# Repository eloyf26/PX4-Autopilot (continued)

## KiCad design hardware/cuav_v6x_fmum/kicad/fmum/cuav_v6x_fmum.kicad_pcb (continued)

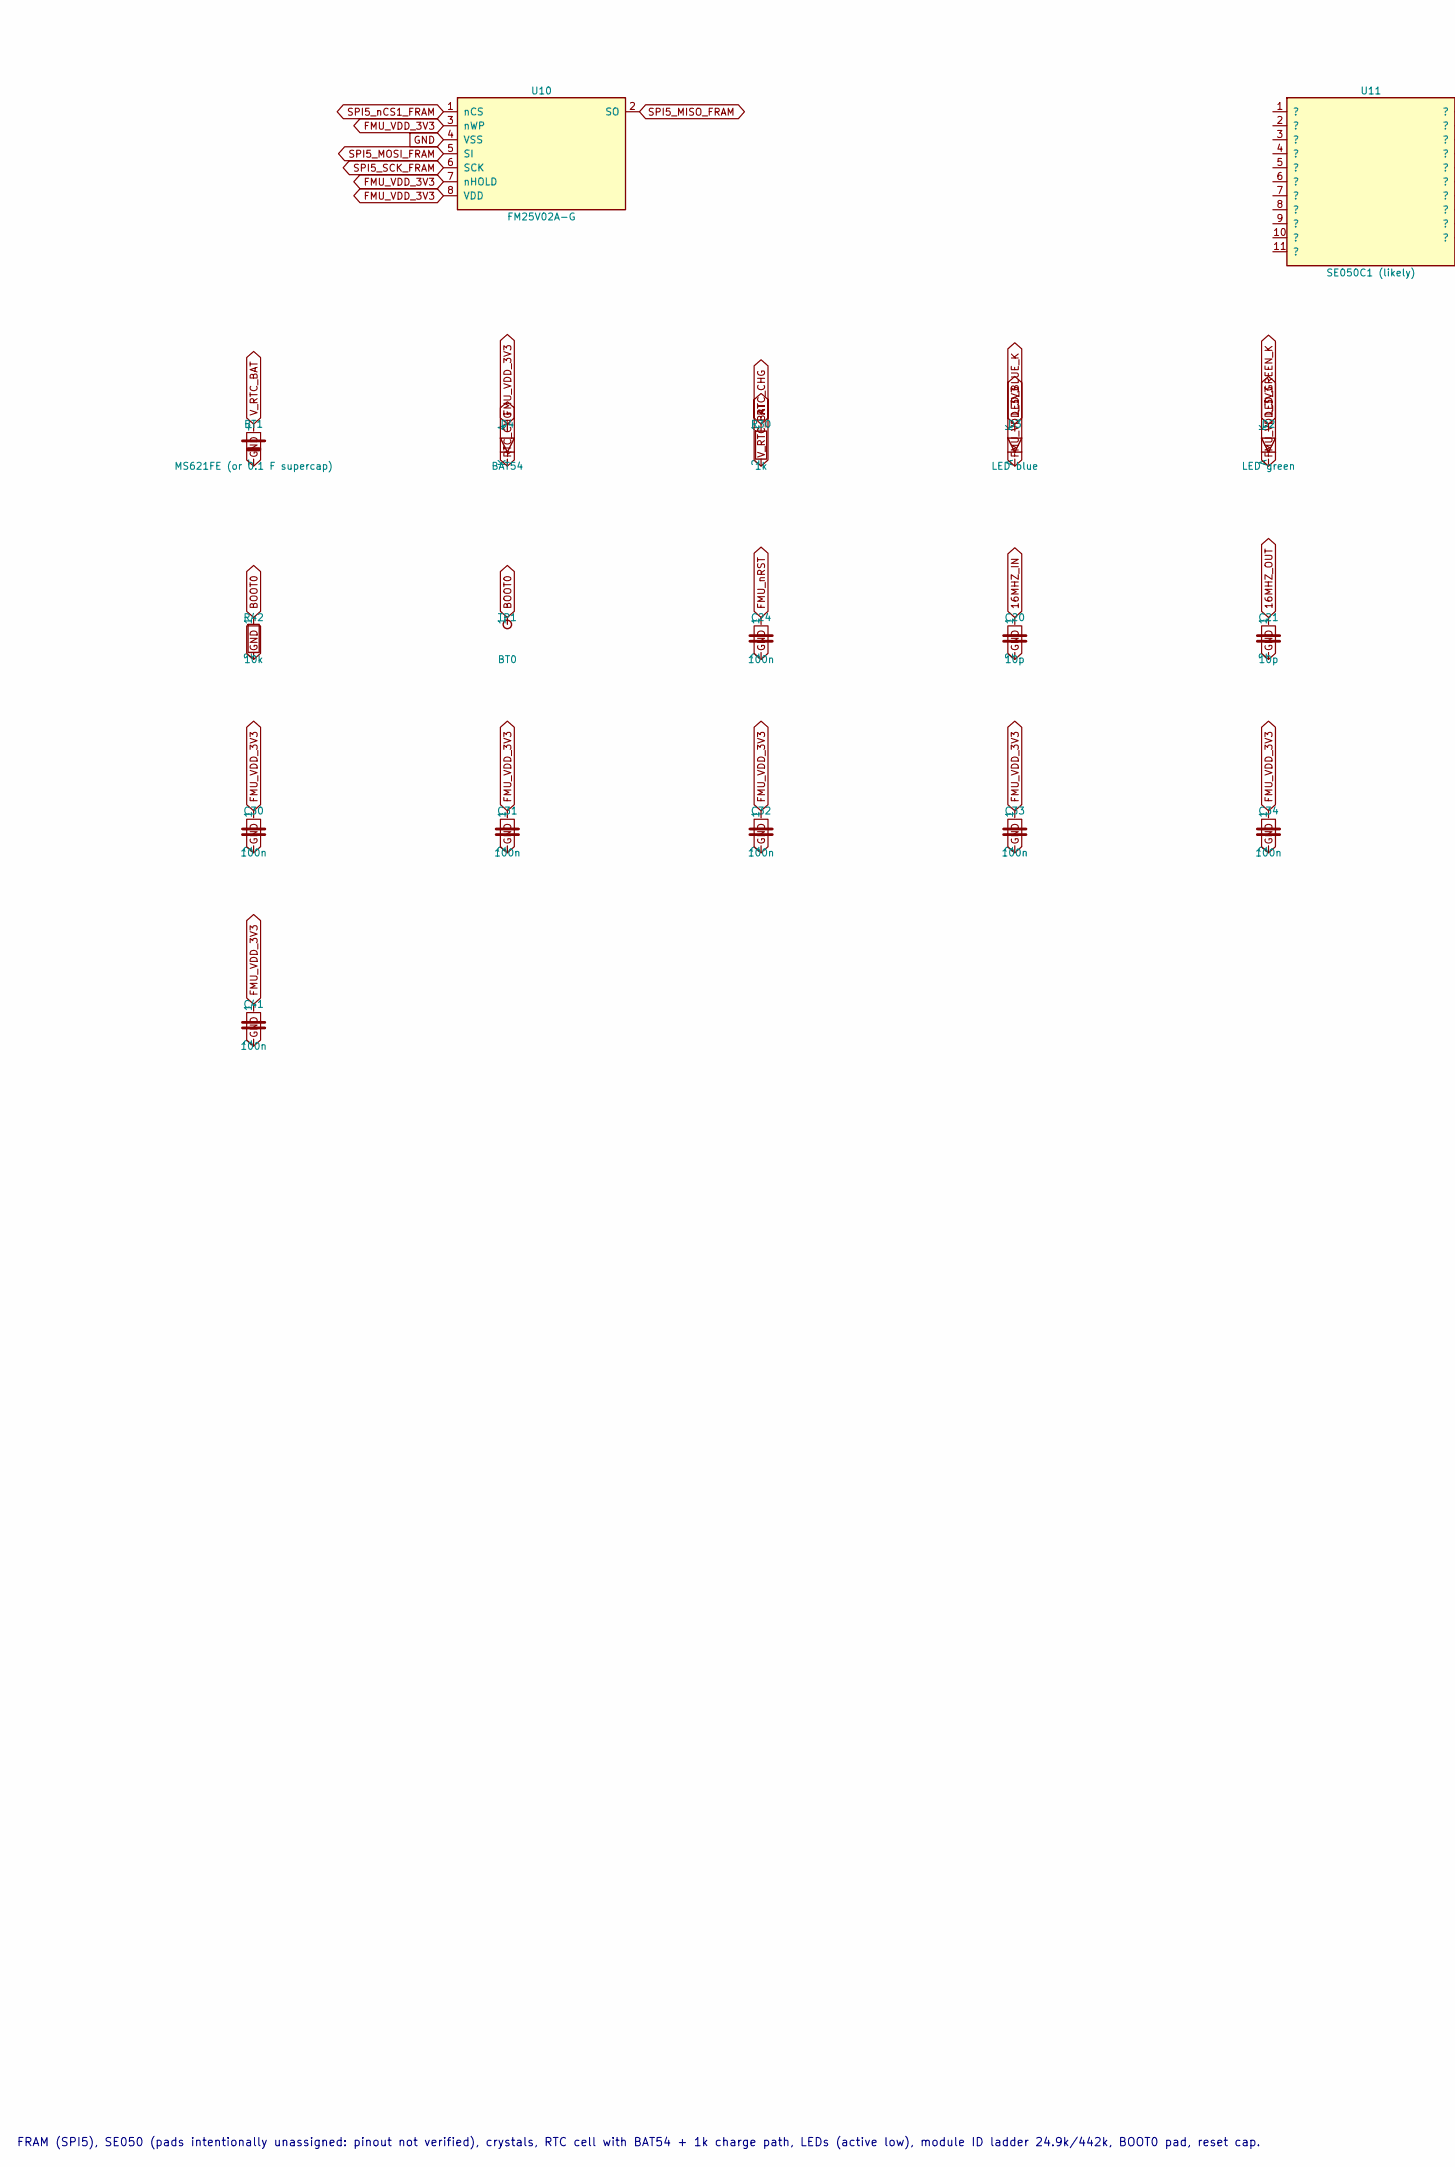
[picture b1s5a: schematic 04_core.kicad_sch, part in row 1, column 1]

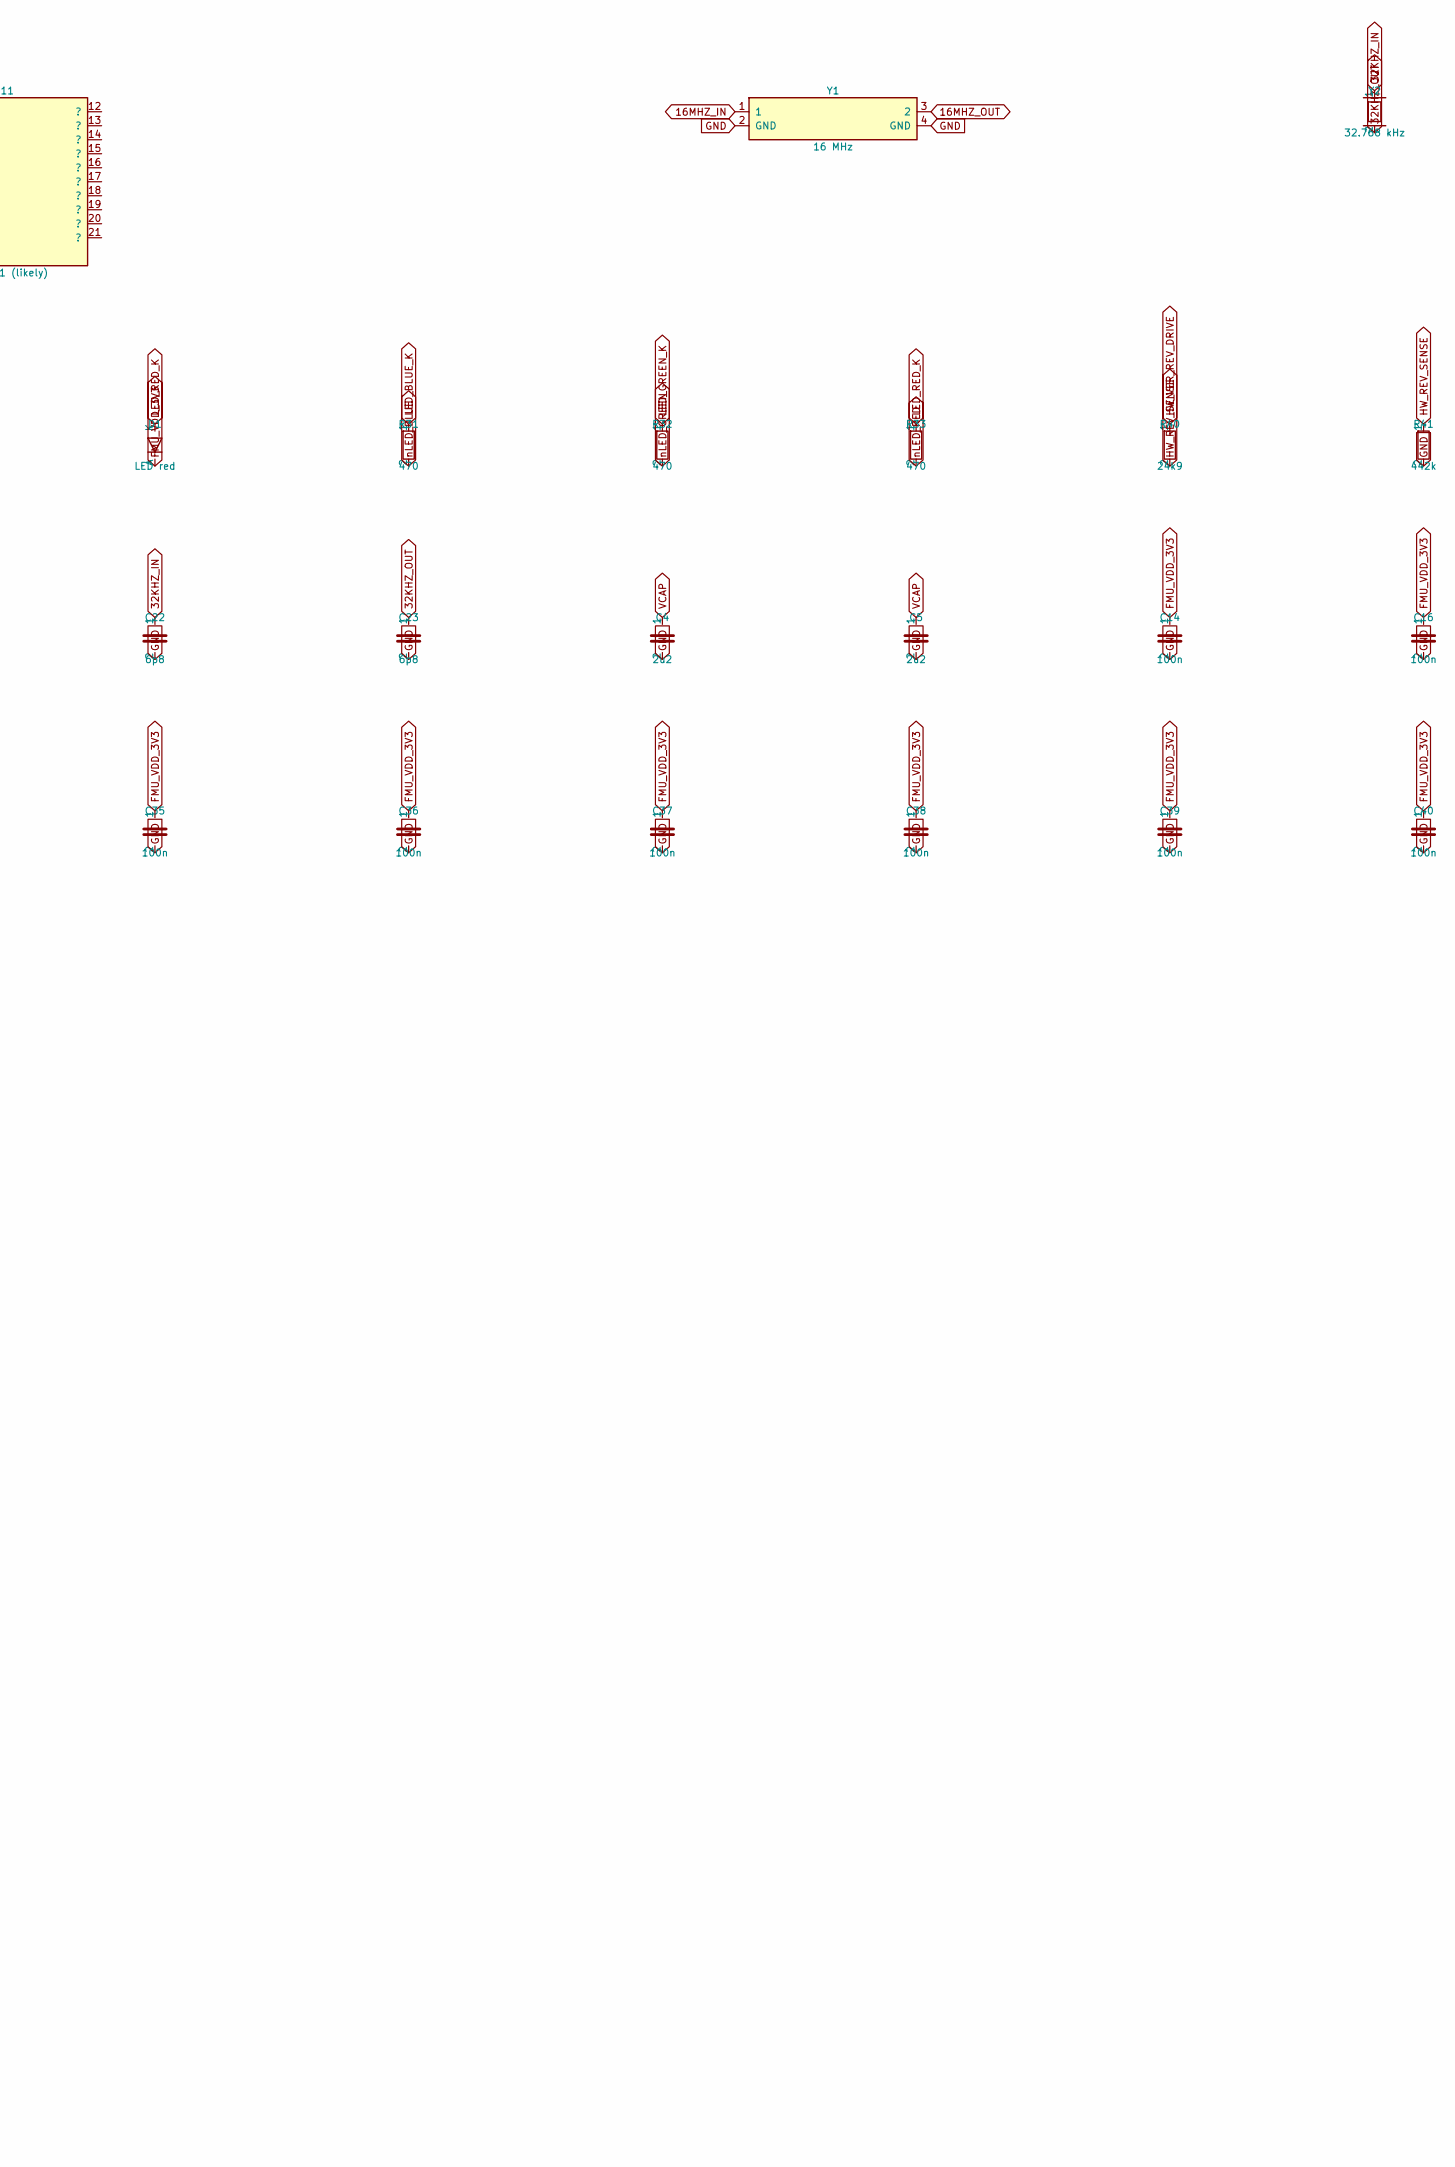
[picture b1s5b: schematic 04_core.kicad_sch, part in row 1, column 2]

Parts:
BT1: MS621FE (or 0.1 F supercap); Seiko_MS621FE
C4, C5: 2u2; C_0402_1005Metric
C14, C16, C24, C30, C31, C32, C33, C34, C35, C36, C37, C38, C39, C40, C41: 100n; C_0402_1005Metric
C20, C21: 10p; C_0402_1005Metric
C22, C23: 6p8; C_0402_1005Metric
D1: LED red; LED_0603_1608Metric
D2: LED green; LED_0603_1608Metric
D3: LED blue; LED_0603_1608Metric
D4: BAT54; D_SOD-323
R30: 1k; R_0402_1005Metric
R31, R32, R33: 470; R_0402_1005Metric
R40: 24k9; R_0402_1005Metric
R41: 442k; R_0402_1005Metric
R42: 10k; R_0402_1005Metric
TP1: BT0; TestPad_1.0mm
U10: FM25V02A-G; SOIC-8_3.9x4.9mm_P1.27mm
U11: SE050C1 (likely); QFN-20-1EP_3x3mm_P0.4mm_EP1.65x1.65mm
Y1: 16 MHz; Crystal_SMD_3225-4Pin_3.2x2.5mm
Y2: 32.768 kHz; Crystal_SMD_3215-2Pin_3.2x1.5mm

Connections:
16MHZ_IN: C20.1, Y1.1; also elsewhere on the board
16MHZ_OUT: C21.1, Y1.3 (2); also elsewhere on the board
32KHZ_IN: C22.1, Y2.1; also elsewhere on the board
32KHZ_OUT: C23.1, Y2.2; also elsewhere on the board
BOOT0: R42.1, TP1.1; also elsewhere on the board
FMU_VDD_3V3: C14.1, C16.1, C30.1, C31.1, C32.1, C33.1, C34.1, C35.1, C36.1, C37.1, C38.1, C39.1, C40.1, C41.1, D1.2 (A), D2.2 (A), D3.2 (A), D4.1 (A), U10.3 (nWP), U10.7 (nHOLD), U10.8 (VDD); also elsewhere on the board
FMU_nRST: C24.1; also elsewhere on the board
GND: BT1.2 (-), C4.2, C5.2, C14.2, C16.2, C20.2, C21.2, C22.2, C23.2, C24.2, C30.2, C31.2, C32.2, C33.2, C34.2, C35.2, C36.2, C37.2, C38.2, C39.2, C40.2, C41.2, R41.2, R42.2, U10.4 (VSS), Y1.2 (GND), Y1.4 (GND); also elsewhere on the board
HW_REV_SENSE: R40.2, R41.1; also elsewhere on the board
HW_VER_REV_DRIVE: R40.1; also elsewhere on the board
LED_BLUE_K: D3.1 (K), R31.1
LED_GREEN_K: D2.1 (K), R32.1
LED_RED_K: D1.1 (K), R33.1
RTC_CHG: D4.2 (K), R30.1
SPI5_MISO_FRAM: U10.2 (SO); also elsewhere on the board
SPI5_MOSI_FRAM: U10.5 (SI); also elsewhere on the board
SPI5_SCK_FRAM: U10.6 (SCK); also elsewhere on the board
SPI5_nCS1_FRAM: U10.1 (nCS); also elsewhere on the board
VCAP: C4.1, C5.1; also elsewhere on the board
V_RTC_BAT: BT1.1 (+), R30.2; also elsewhere on the board
nLED_BLUE: R31.2; also elsewhere on the board
nLED_GREEN: R32.2; also elsewhere on the board
nLED_RED: R33.2; also elsewhere on the board

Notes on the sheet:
FRAM (SPI5), SE050 (pads intentionally unassigned: pinout not verified), crystals, RTC cell with BAT54 + 1k charge path, LEDs (active low), module ID ladder 24.9k/442k, BOOT0 pad, reset cap.

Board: 6 copper layers, 96 parts (55 on the bottom side), 150 nets, no tracks yet.

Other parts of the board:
H1, H2, H3, H4: M2 GND; HOLE

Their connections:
GND: H1.1, H2.1, H3.1, H4.1; also elsewhere on the board

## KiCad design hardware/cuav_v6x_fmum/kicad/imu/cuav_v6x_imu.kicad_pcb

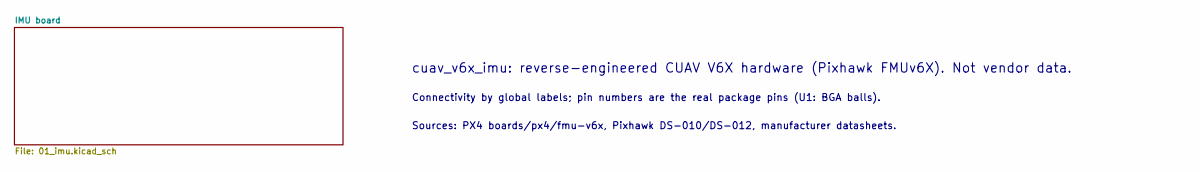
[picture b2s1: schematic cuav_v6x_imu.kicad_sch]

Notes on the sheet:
cuav_v6x_imu: reverse-engineered CUAV V6X hardware (Pixhawk FMUv6X). Not vendor data.
Connectivity by global labels; pin numbers are the real package pins (U1: BGA balls).
Sources: PX4 boards/px4/fmu-v6x, Pixhawk DS-010/DS-012, manufacturer datasheets.

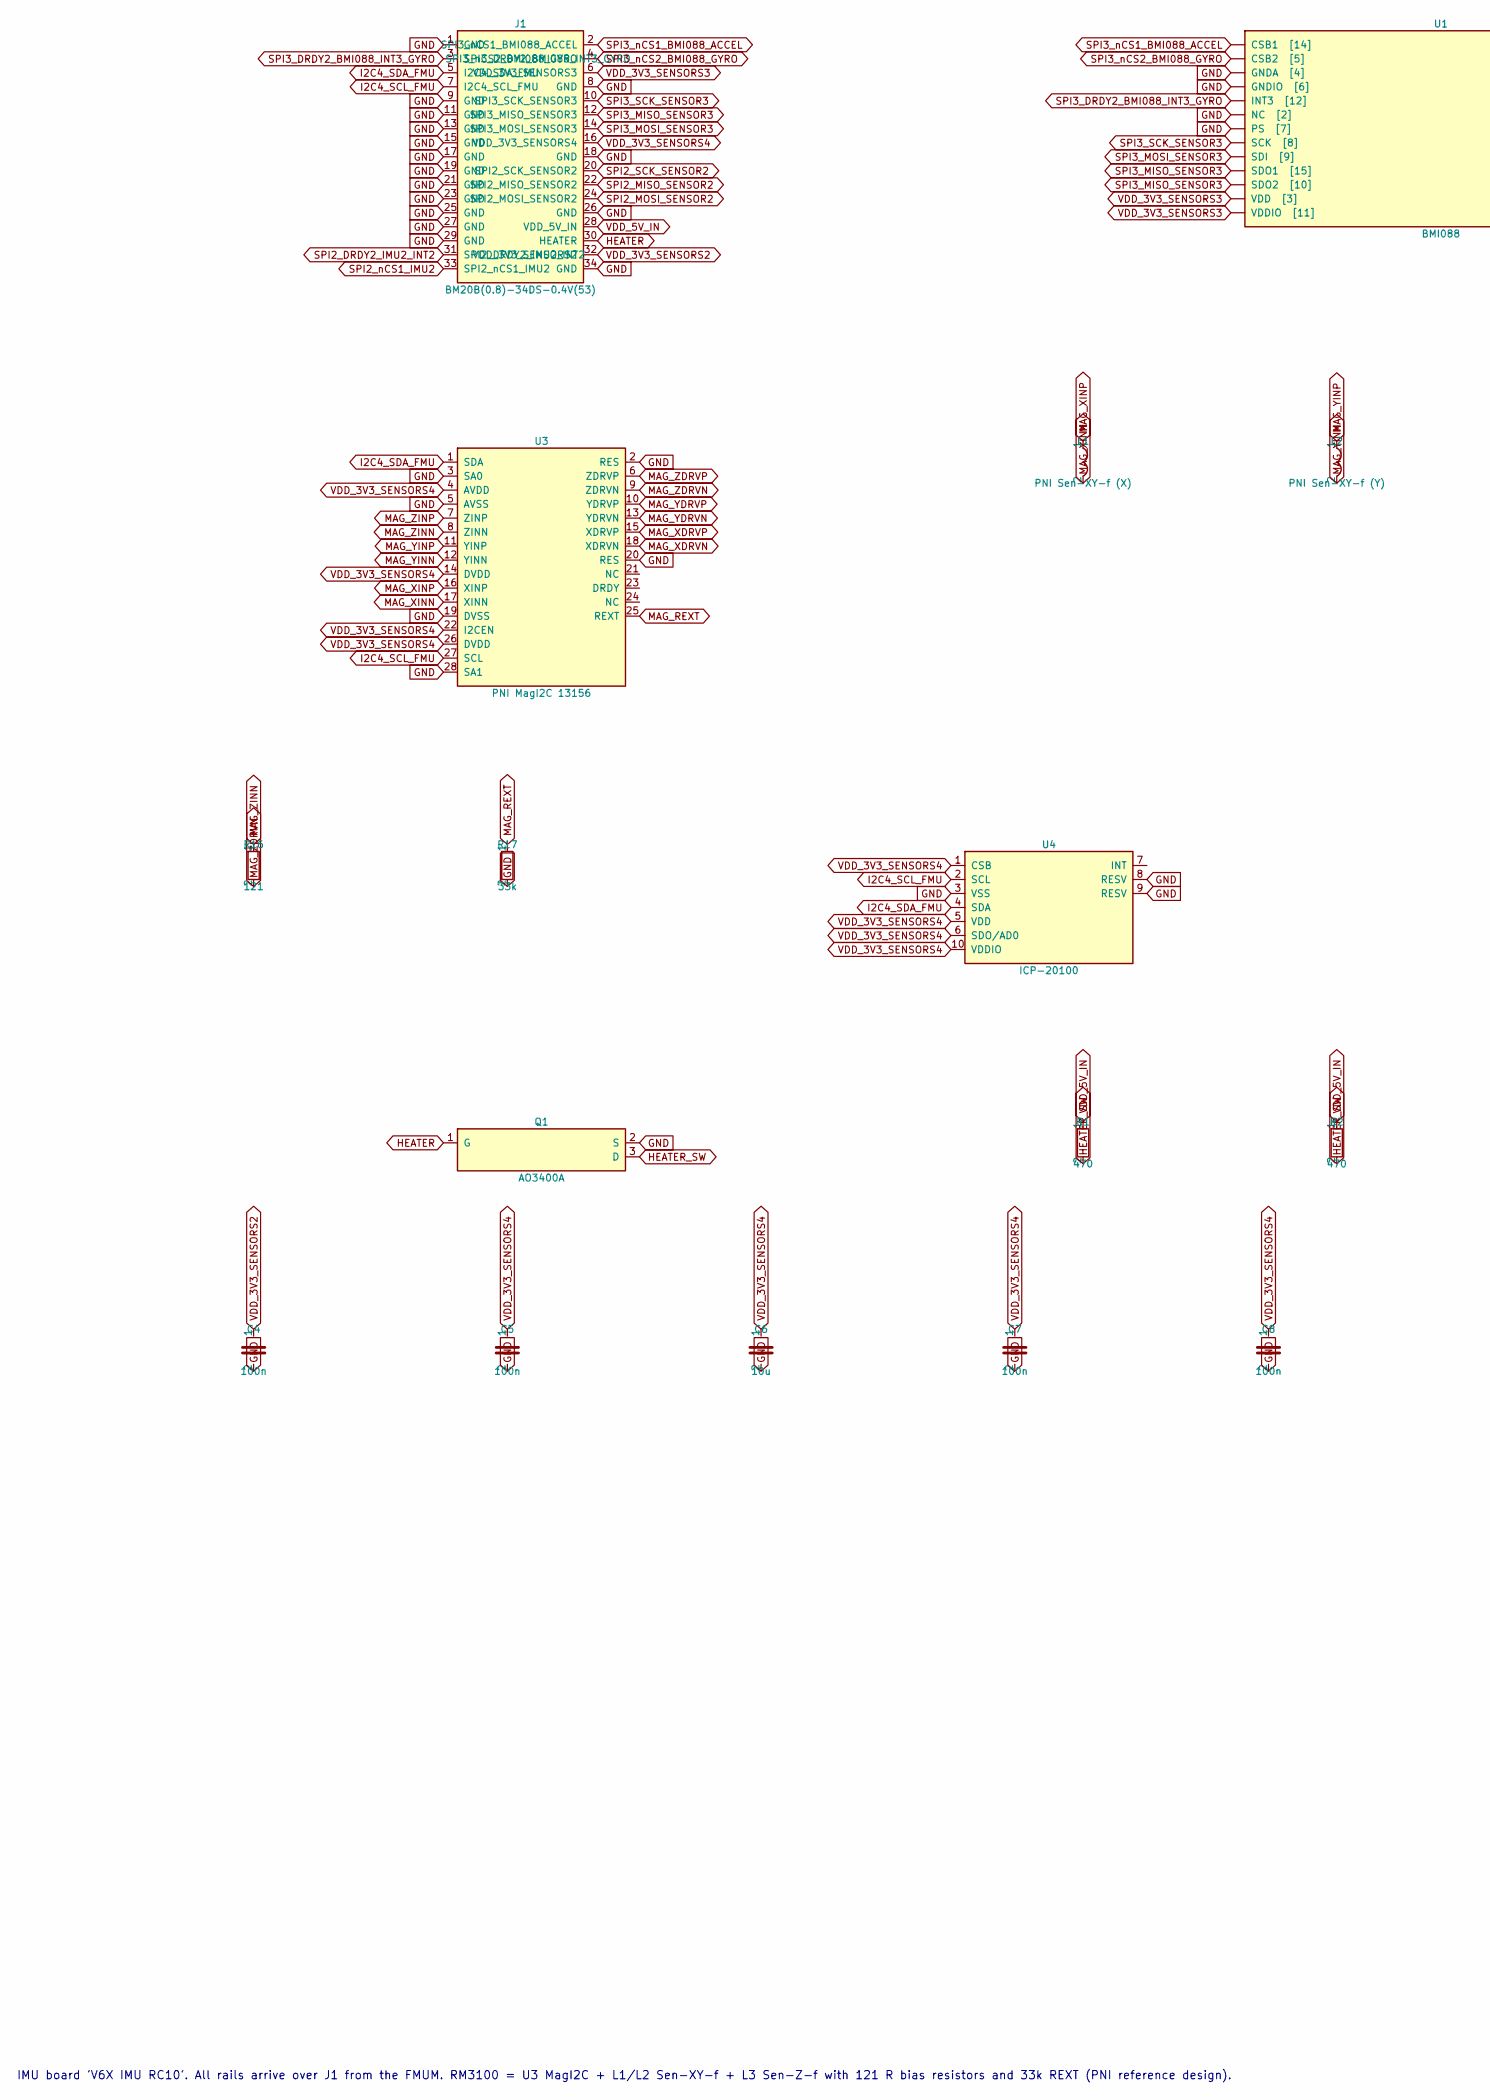
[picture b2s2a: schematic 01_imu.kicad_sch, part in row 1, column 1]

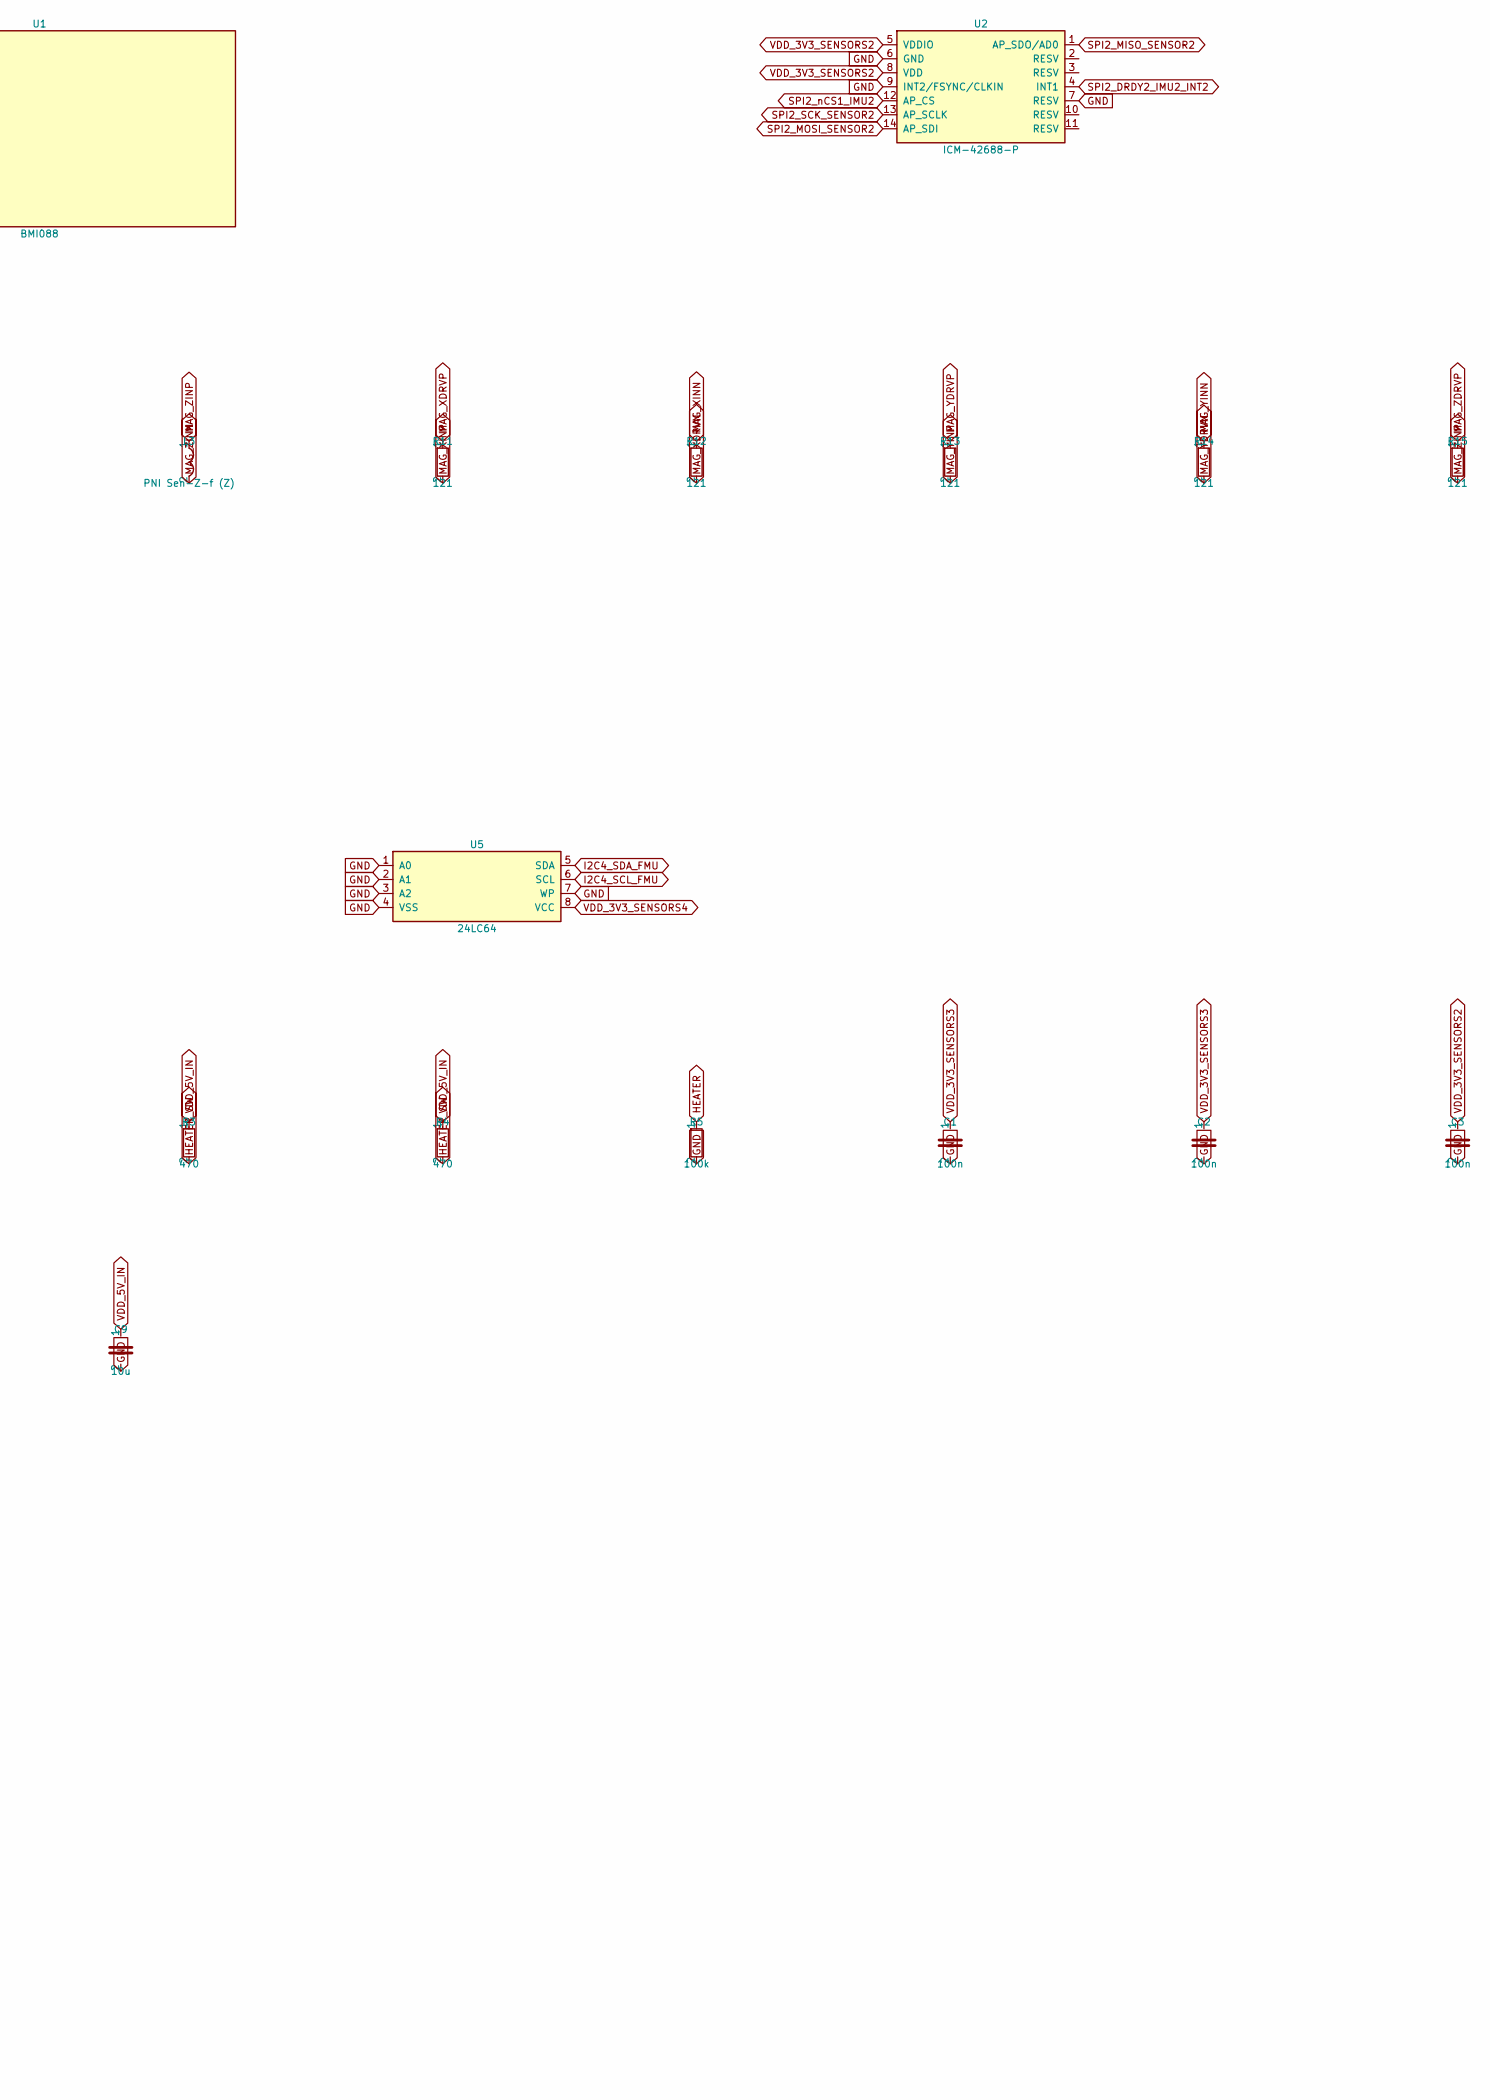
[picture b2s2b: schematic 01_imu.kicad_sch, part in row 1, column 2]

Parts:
C1, C2, C3, C4, C5, C7, C8: 100n; C_0402_1005Metric
C6, C9: 10u; C_0603_1608Metric
J1: BM20B(0.8)-34DS-0.4V(53); Hirose_BM20B-34-0.4V
L1: PNI Sen-XY-f (X); PNI_Sen-XY-f
L2: PNI Sen-XY-f (Y); PNI_Sen-XY-f
L3: PNI Sen-Z-f (Z); PNI_Sen-Z-f
Q1: AO3400A; SOT-23
R1, R2, R3, R4: 470; R_0805_2012Metric
R5: 100k; R_0402_1005Metric
R11, R12, R13, R14, R15, R16: 121; R_0402_1005Metric
R17: 33k; R_0402_1005Metric
U1: BMI088; Bosch_LGA-16_4.5x3mm_P0.5mm
U2: ICM-42688-P; LGA-14_3x2.5mm_P0.5mm_LayoutBorder3x4y
U3: PNI MagI2C 13156; PNI_MLF-28_4x4mm_P0.4mm
U4: ICP-20100; TDK_LGA-10_2x2mm_P0.5mm
U5: 24LC64; SOIC-8_3.9x4.9mm_P1.27mm

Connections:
GND: C1.2, C2.2, C3.2, C4.2, C5.2, C6.2, C7.2, C8.2, C9.2, J1.1 (GND), J1.8 (GND), J1.9 (GND), J1.11 (GND), J1.13 (GND), J1.15 (GND), J1.17 (GND), J1.18 (GND), J1.19 (GND), J1.21 (GND), J1.23 (GND), J1.25 (GND), J1.26 (GND), J1.27 (GND), J1.29 (GND), J1.34 (GND), Q1.2 (S), R5.2, R17.2, U1.2 (NC [2]), U1.4 (GNDA [4]), U1.6 (GNDIO [6]), U1.7 (PS [7]), U2.6 (GND), U2.7 (RESV), U2.9 (INT2/FSYNC/CLKIN), U3.2 (RES), U3.3 (SA0), U3.5 (AVSS), U3.19 (DVSS), U3.20 (RES), U3.28 (SA1), U4.3 (VSS), U4.8 (RESV), U4.9 (RESV), U5.1 (A0), U5.2 (A1), U5.3 (A2), U5.4 (VSS), U5.7 (WP); also elsewhere on the board
HEATER: J1.30 (HEATER), Q1.1 (G), R5.1
HEATER_SW: Q1.3 (D), R1.2, R2.2, R3.2, R4.2
I2C4_SCL_FMU: J1.7 (I2C4_SCL_FMU), U3.27 (SCL), U4.2 (SCL), U5.6 (SCL)
I2C4_SDA_FMU: J1.5 (I2C4_SDA_FMU), U3.1 (SDA), U4.4 (SDA), U5.5 (SDA)
MAG_REXT: R17.1, U3.25 (REXT)
MAG_XDRVN: R12.2, U3.18 (XDRVN)
MAG_XDRVP: R11.1, U3.15 (XDRVP)
MAG_XINN: L1.2, R12.1, U3.17 (XINN)
MAG_XINP: L1.1, R11.2, U3.16 (XINP)
MAG_YDRVN: R14.2, U3.13 (YDRVN)
MAG_YDRVP: R13.1, U3.10 (YDRVP)
MAG_YINN: L2.2, R14.1, U3.12 (YINN)
MAG_YINP: L2.1, R13.2, U3.11 (YINP)
MAG_ZDRVN: R16.2, U3.9 (ZDRVN)
MAG_ZDRVP: R15.1, U3.6 (ZDRVP)
MAG_ZINN: L3.2, R16.1, U3.8 (ZINN)
MAG_ZINP: L3.1, R15.2, U3.7 (ZINP)
SPI2_DRDY2_IMU2_INT2: J1.31 (SPI2_DRDY2_IMU2_INT2), U2.4 (INT1)
SPI2_MISO_SENSOR2: J1.22 (SPI2_MISO_SENSOR2), U2.1 (AP_SDO/AD0)
SPI2_MOSI_SENSOR2: J1.24 (SPI2_MOSI_SENSOR2), U2.14 (AP_SDI)
SPI2_SCK_SENSOR2: J1.20 (SPI2_SCK_SENSOR2), U2.13 (AP_SCLK)
SPI2_nCS1_IMU2: J1.33 (SPI2_nCS1_IMU2), U2.12 (AP_CS)
SPI3_DRDY2_BMI088_INT3_GYRO: J1.3 (SPI3_DRDY2_BMI088_INT3_GYRO), U1.12 (INT3 [12])
SPI3_MISO_SENSOR3: J1.12 (SPI3_MISO_SENSOR3), U1.10 (SDO2 [10]), U1.15 (SDO1 [15])
SPI3_MOSI_SENSOR3: J1.14 (SPI3_MOSI_SENSOR3), U1.9 (SDI [9])
SPI3_SCK_SENSOR3: J1.10 (SPI3_SCK_SENSOR3), U1.8 (SCK [8])
SPI3_nCS1_BMI088_ACCEL: J1.2 (SPI3_nCS1_BMI088_ACCEL), U1.14 (CSB1 [14])
SPI3_nCS2_BMI088_GYRO: J1.4 (SPI3_nCS2_BMI088_GYRO), U1.5 (CSB2 [5])
VDD_3V3_SENSORS2: C3.1, C4.1, J1.32 (VDD_3V3_SENSORS2), U2.5 (VDDIO), U2.8 (VDD)
VDD_3V3_SENSORS3: C1.1, C2.1, J1.6 (VDD_3V3_SENSORS3), U1.3 (VDD [3]), U1.11 (VDDIO [11])
VDD_3V3_SENSORS4: C5.1, C6.1, C7.1, C8.1, J1.16 (VDD_3V3_SENSORS4), U3.4 (AVDD), U3.14 (DVDD), U3.22 (I2CEN), U3.26 (DVDD), U4.1 (CSB), U4.5 (VDD), U4.6 (SDO/AD0), U4.10 (VDDIO), U5.8 (VCC)
VDD_5V_IN: C9.1, J1.28 (VDD_5V_IN), R1.1, R2.1, R3.1, R4.1

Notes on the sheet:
IMU board 'V6X IMU RC10'. All rails arrive over J1 from the FMUM. RM3100 = U3 MagI2C + L1/L2 Sen-XY-f + L3 Sen-Z-f with 121 R bias resistors and 33k REXT (PNI reference design).

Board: 4 copper layers, 37 parts (12 on the bottom side), 33 nets, no tracks yet.

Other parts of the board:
H1, H2: 2.2 mm; NPTH
M1, M2, M3, M4: GND pad; MPAD

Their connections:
GND: M1.1, M2.1, M3.1, M4.1; also elsewhere on the board

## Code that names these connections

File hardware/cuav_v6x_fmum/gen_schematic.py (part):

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# --------------------------------------------------------------------------
PINS = [
    # ---- Port A
    ("PA0",  "ADC1_INP16",        "SCALED_VDD_3V3_SENSORS1", "R-divider on VDD_3V3_SENSORS1"),
    ("PA1",  "ETH_REF_CLK",       "ETH_REF_CLK",             "X2-3"),
    ("PA2",  "ETH_MDIO",          "ETH_MDIO",                "X2-2"),
    ("PA3",  "USART2_RX",         "USART2_RX_TELEM3",        "X1-42"),
    ("PA4",  "ADC12_INP18",       "SCALED_VDD_3V3_SENSORS2", "R-divider on VDD_3V3_SENSORS2"),
    ("PA5",  "SPI1_SCK",          "SPI1_SCK_SENSOR1",        "U_IMU3 ICM-20649 SCLK"),
    ("PA6",  "SPI6_MISO",         "SPI6_MISO_EXTERNAL1",     "X2-31"),
    ("PA7",  "ETH_CRS_DV",        "ETH_CRS_DV",              "X2-7"),
    ("PA8",  "I2C3_SCL",          "I2C3_SCL_BASE",           "X1-10"),
    ("PA9",  "OTG_FS_VBUS",       "VBUS_SENSE",              "X1-80"),
    ("PA10", "GPIO in (EXTI)",    "SPI2_DRDY2_IMU2_INT2",    "J3-31"),
    ("PA11", "OTG_FS_DM",         "USB_D_N",                 "X1-78"),
    ("PA12", "OTG_FS_DP",         "USB_D_P",                 "X1-76"),
    ("PA13", "SWDIO",             "FMU_SWDIO",               "X1-75"),
    ("PA14", "SWCLK",             "FMU_SWCLK",               "X1-77"),
    ("PA15", "GPIO out",          "SPI6_nCS2_EXTERNAL1",     "X2-43"),
    # ---- Port B
    ("PB0",  "ADC12_INP9",        "SCALED_VDD_3V3_SENSORS3", "R-divider on VDD_3V3_SENSORS3"),
    ("PB1",  "ADC12_INP5",        "SCALED_V5",               "R-divider on VDD_5V_IN"),
    ("PB2",  "SPI3_MOSI",         "SPI3_MOSI_SENSOR3",       "J3-14"),
    ("PB3",  "SPI6_SCK / SWO",    "SPI6_SCK_EXTERNAL1",      "X2-35"),
    ("PB4",  "SDMMC2_D3",         "SD_D3",                   "J4 microSD DAT3"),
    ("PB5",  "SPI1_MOSI",         "SPI1_MOSI_SENSOR1",       "U_IMU3 ICM-20649 SDI"),
    ("PB6",  "USART1_TX",         "USART1_TX_GPS1",          "X1-36"),
    ("PB7",  "USART1_RX",         "USART1_RX_GPS1",          "X1-34"),
    ("PB8",  "I2C1_SCL",          "I2C1_SCL_BASE",           "X1-18"),
    ("PB9",  "I2C1_SDA",          "I2C1_SDA_BASE",           "X1-16"),
    ("PB10", "GPIO out (TIM2_CH3)", "HEATER",                "J3-30"),
    ("PB11", "ETH_TX_EN",         "ETH_TX_EN",               "X2-27"),
    ("PB12", "FDCAN2_RX",         "CAN2_RX",                 "X1-59"),
    ("PB13", "FDCAN2_TX",         "CAN2_TX",                 "X1-57"),
    ("PB14", "SDMMC2_D0",         "SD_D0",                   "J4 microSD DAT0"),
    ("PB15", "SDMMC2_D1",         "SD_D1",                   "J4 microSD DAT1"),
    # ---- Port C
    ("PC0",  "GPIO in (EXTI)",    "NFC_GPIO",                "X2-48"),
    ("PC1",  "ETH_MDC",           "ETH_MDC",                 "X2-4"),
    ("PC2",  "ADC3_INP12 (PC2_C)", "ADC1_6V6",               "X1-90"),
    ("PC3",  "ADC3_INP13 (PC3_C)", "ADC1_3V3",               "X1-92"),
    ("PC4",  "ETH_RXD0",          "ETH_RXD0",                "X2-11"),
    ("PC5",  "ETH_RXD1",          "ETH_RXD1",                "X2-15"),
    ("PC6",  "USART6_TX",         "USART6_TX_TO_IO",         "X1-72"),
    ("PC7",  "USART6_RX",         "USART6_RX_FROM_IO_RC",    "X1-70"),
    ("PC8",  "UART5_RTS",         "UART5_RTS_TELEM2",        "X1-58"),
    ("PC9",  "UART5_CTS",         "UART5_CTS_TELEM2",        "X1-60"),
    ("PC10", "SPI3_SCK",          "SPI3_SCK_SENSOR3",        "J3-10"),
    ("PC11", "SPI3_MISO",         "SPI3_MISO_SENSOR3",       "J3-12"),
    ("PC12", "UART5_TX",          "UART5_TX_TELEM2",         "X1-52"),
    ("PC13", "GPIO out",          "VDD_3V3_SD_CARD_EN",      "Q_SD load switch EN"),
    ("PC14", "OSC32_IN",          "32KHZ_IN",                "Y2 32.768 kHz"),
    ("PC15", "OSC32_OUT",         "32KHZ_OUT",               "Y2 32.768 kHz"),
    # ---- Port D
    ("PD0",  "FDCAN1_RX",         "CAN1_RX",                 "X1-65"),
    ("PD1",  "FDCAN1_TX",         "CAN1_TX",                 "X1-63"),
    ("PD2",  "UART5_RX",          "UART5_RX_TELEM2",         "X1-54"),
    ("PD3",  "USART2_CTS",        "USART2_CTS_TELEM3",       "X1-48"),
    ("PD4",  "USART2_RTS",        "USART2_RTS_TELEM3",       "X1-46"),
    ("PD5",  "USART2_TX",         "USART2_TX_TELEM3",        "X1-40"),
    ("PD6",  "SDMMC2_CK",         "SD_CLK",                  "J4 microSD CLK"),
    ("PD7",  "SDMMC2_CMD",        "SD_CMD",                  "J4 microSD CMD"),
    ("PD8",  "USART3_TX",         "USART3_TX_DEBUG",         "X1-69"),
    ("PD9",  "USART3_RX",         "USART3_RX_DEBUG",         "X1-71"),
    ("PD10", "GPIO out",          "FMU_nSAFETY_SWITCH_LED_OUT", "X1-23"),
    ("PD11", "GPIO in",           "SPI6_DRDY1_EXTERNAL1",    "X2-47"),
    ("PD12", "GPIO in",           "SPI6_DRDY2_EXTERNAL1",    "X2-45"),
    ("PD13", "TIM4_CH2",          "FMU_CH5",                 "X1-7"),
    ("PD14", "TIM4_CH3",          "FMU_CH6",                 "X1-5"),
    ("PD15", "GPIO in (spare)",   "PD15_SPARE",              "NC"),
    # ---- Port E
    ("PE0",  "UART8_RX",          "UART8_RX_GPS2",           "X1-30"),
    ("PE1",  "UART8_TX",          "UART8_TX_GPS2",           "X1-28"),
    ("PE2",  "TRACECLK",          "TRACECLK",                "J1 TRACE-1"),
    ("PE3",  "GPIO od (TRACED0)", "nLED_RED",                "D1 red LED cathode (+ J1 TRACE-3)"),
    ("PE4",  "GPIO od (TRACED1)", "nLED_GREEN",              "D2 green LED cathode (+ J1 TRACE-5)"),
    ("PE5",  "GPIO od (TRACED2)", "nLED_BLUE",               "D3 blue LED cathode (+ J1 TRACE-7)"),
    ("PE6",  "GPIO (TRACED3)",    "nARMED",                  "X1-85 (+ J1 TRACE-8)"),
    ("PE7",  "GPIO out",          "VDD_3V3_SENSORS3_EN",     "U_LDO3 EN"),
    ("PE8",  "UART7_TX",          "UART7_TX_TELEM1",         "X1-64"),
    ("PE9",  "GPIO out",          "SPIX_SYNC",               "X2-49"),
    ("PE10", "UART7_CTS",         "UART7_CTS_TELEM1",        "X1-24"),
    ("PE11", "TIM1_CH2 (capture)", "FMU_CAP1",               "X1-97"),
    ("PE15", "GPIO in",           "VDD_5V_PERIPH_nOC",       "X1-37"),
    # ---- Port F
    ("PF0",  "I2C2_SDA",          "I2C2_SDA_BASE",           "X1-12 (+ U_BARO2 ICP-20100 SDA)"),
    ("PF1",  "I2C2_SCL",          "I2C2_SCL_BASE",           "X1-14 (+ U_BARO2 ICP-20100 SCL)"),
    ("PF2",  "GPIO in (EXTI)",    "SPI1_DRDY1_IMU3_INT1",    "U_IMU3 ICM-20649 INT1"),
    ("PF4",  "GPIO out",          "VDD_3V3_SENSORS2_EN",     "U_LDO2 EN"),
    ("PF5",  "GPIO in (pull-up)", "FMU_SAFETY_SWITCH_IN",    "X1-21"),
    ("PF6",  "UART7_RX",          "UART7_RX_TELEM1",         "X1-66"),
    ("PF7",  "SPI5_SCK",          "SPI5_SCK_FRAM",           "U_FRAM FM25V02A SCK"),
    ("PF8",  "UART7_RTS",         "UART7_RTS_TELEM1",        "X1-22"),
    ("PF9",  "TIM14_CH1",         "BUZZER_1",                "X1-4"),
    ("PF10", "GPIO out",          "SPI6_nRESET_EXTERNAL1",   "X2-39"),
    ("PF11", "SPI5_MOSI",         "SPI5_MOSI_FRAM",          "U_FRAM FM25V02A SI"),
    ("PF12", "ADC1_INP6",         "SCALED_VDD_3V3_SENSORS4", "R-divider on VDD_3V3_SENSORS4"),
    ("PF13", "GPIO in",           "VDD_5V_HIPOWER_nOC",      "X1-83"),
    ("PF14", "I2C4_SCL",          "I2C4_SCL_FMU",            "J3-7 (+ U_SE SE050 SCL)"),
    ("PF15", "I2C4_SDA",          "I2C4_SDA_FMU",            "J3-5 (+ U_SE SE050 SDA)"),
    # ---- Port G
    ("PG0",  "GPIO out",          "HW_VER_REV_DRIVE",        "X1-25 (+ top of FMUM ID ladder)"),
    ("PG1",  "GPIO in (pull-up)", "nPOWER_IN_A",             "X1-89"),
    ("PG2",  "GPIO in (pull-up)", "nPOWER_IN_B",             "X1-91"),
    ("PG3",  "GPIO in (pull-up)", "nPOWER_IN_C",             "X1-93"),
    ("PG4",  "GPIO out",          "VDD_5V_PERIPH_nEN",       "X1-35"),
    ("PG5",  "GPIO in (EXTI)",    "I2C2_DRDY1_BARO2",        "U_BARO2 ICP-20100 INT (optional)"),
    ("PG6",  "GPIO in (pull-up)", "PG6",                     "X2-44"),
    ("PG7",  "GPIO out",          "SPI5_nCS1_FRAM",          "U_FRAM FM25V02A nCS"),
    ("PG8",  "GPIO out",          "VDD_3V3_SENSORS4_EN",     "U_LDO4 EN"),
    ("PG9",  "SPI1_MISO",         "SPI1_MISO_SENSOR1",       "U_IMU3 ICM-20649 SDO"),
    ("PG10", "GPIO out",          "VDD_5V_HIPOWER_nEN",      "X1-81"),
    ("PG11", "SDMMC2_D2",         "SD_D2",                   "J4 microSD DAT2"),
    ("PG12", "ETH_TXD1",          "ETH_TXD1",                "X2-23"),
    ("PG13", "ETH_TXD0",          "ETH_TXD0",                "X2-19"),
    ("PG14", "SPI6_MOSI",         "SPI6_MOSI_EXTERNAL1",     "X2-33"),
    ("PG15", "GPIO out",          "ETH_POWER_EN",            "X2-6"),
    # ---- Port H
    ("PH0",  "OSC_IN",            "16MHZ_IN",                "Y1 16 MHz"),
    ("PH1",  "OSC_OUT",           "16MHZ_OUT",               "Y1 16 MHz"),
    ("PH2",  "GPIO out",          "VDD_3V3_SPEKTRUM_POWER_EN", "X1-33"),
    ("PH3",  "ADC3_INP14",        "HW_VER_SENSE",            "X1-27 (base-board ID ladder)"),
    ("PH4",  "ADC3_INP15",        "HW_REV_SENSE",            "FMUM ID ladder (R_up 24.9k / R_dn 442k = ID 1)"),
    ("PH5",  "GPIO out",          "SPI2_nCS1_IMU2",          "J3-33"),
    ("PH6",  "TIM12_CH1",         "FMU_CH7",                 "X1-3"),
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
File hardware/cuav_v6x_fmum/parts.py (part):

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            continue
        if dest.startswith("NC"):
            net = ""
        if pin in ("PC2", "PC3"):           # only the _C balls exist on this package
            b = ball(pin + "_C")
        else:
            b = ball(pin)
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            et = "output"
        pins.append((b, pin, net, et))
    # oscillators / special
    pins += [(ball("NRST"), "NRST", "FMU_nRST", "input"), (ball("BOOT0"), "BOOT0", "BOOT0", "input"),
             (ball("VBAT"), "VBAT", "V_RTC_BAT", "power_in"), (ball("PDR_ON"), "PDR_ON", V33, "input"),
             (ball("VDDA"), "VDDA", V33, "power_in"), (ball("VSSA"), "VSSA", GND, "power_in"),
             (ball("VREF+"), "VREF+", V33, "power_in"), (ball("VREF"), "VREF-", GND, "power_in"),
             (ball("VDD33_USB"), "VDD33_USB", V33, "power_in")]
    for b in sorted(set(BALLS["VCAP"])):
        pins.append((b, "VCAP", "VCAP", "passive"))
    for b in sorted(set(BALLS["VDD"])):
        pins.append((b, "VDD", V33, "power_in"))
    for b in sorted(set(BALLS["VSS"])):
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    P("U11", "SE050C1 (likely)", "lib:QFN-20-1EP_3x3mm_P0.4mm_EP1.65x1.65mm", "F", 23.3, 11.4, 0,
      [(str(i), "?", "", "passive") for i in range(1, 22)],
      "secure element, I2C4 0x48. Pin assignment not available -> pads left unassigned", "ic",
      verify="SE050 HX2QFN20 pinout not verified; connect SDA=I2C4_SDA_FMU, SCL=I2C4_SCL_FMU, VDD/VIN=FMU_VDD_3V3, ENA=FMU_VDD_3V3 per NXP datasheet"),
    P("U8", "ICM-20649", "lib:QFN-24-1EP_3x3mm_P0.4mm_EP1.75x1.6mm", "B", 15.6, 2.3, 0,
      [("7", "AUX_CL", "", "passive"), ("8", "VDDIO", "VDD_3V3_SENSORS1", "power_in"), ("9", "SDO/AD0", "SPI1_MISO_SENSOR1", "output"),
       ("10", "REGOUT", "IMU3_REGOUT", "passive"), ("11", "FSYNC", GND, "input"), ("12", "INT1", "SPI1_DRDY1_IMU3_INT1", "output"),
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
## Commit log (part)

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2026-01-15 fix: disable UXRCE_DDS_SYNCT for Gazebo time sync
    Set UXRCE_DDS_SYNCT=0 in 4001_gz_x500 airframe to keep PX4 timestamps
    in raw simulation time, matching the ROS2 /clock topic when
    use_sim_time:=true is enabled.
2026-01-17 chore: ignore runtime generated files
2026-02-17 wip: disable GstCameraSystem, update gz models submodule
    - Comment out GstCameraSystem plugin in gz_bridge/server.config
    (conflicts with sim_cam_adapter streaming on same UDP port)
    - Update gz submodule with camera model and physics changes
    Core simulation streaming functional.
2026-03-31 feat: broadcast mavlink to other ports for simulated-radar purposes
2026-04-01 feat: add mavlink bidirectional on port 14570 for simulation
